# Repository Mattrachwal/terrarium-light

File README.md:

# Terrarium Light

techplants first electronic device

## Goal

A small low power terrarium light designed to sit on top of mini terrariums. 8x8x8 is probable max size of terrarium this would be usefull on.

## Parts List

ALED7709ATR

SPMWHD32AMH0XAR0PR

AL8860WT
https://www.diodes.com/assets/Datasheets/AL8860.pdf

CH340C

UMH3N
https://fscdn.rohm.com/en/products/databook/datasheet/discrete/transistor/digital/umh3ntn-e.pdf

TPS61169DCKR
https://www.ti.com/product/TPS61169

LDO voltage regulator

https://www.lcsc.com/datasheet/lcsc_datasheet_1811131510_MICRONE-Nanjing-Micro-One-Elec-ME6211C33M5G-N_C82942.pdf

This is the typical LDO used ona lot of dev boards
using the TO-263 for thermal reason, its overkill but i dont know how hot the whole board will be with the LEDS

HGSEMI LM1117S-3.3/TR
https://www.lcsc.com/datasheet/lcsc_datasheet_2209211201_HGSEMI-LM1117S-3-3-TR_C498315.pdf

NSR0240P2
https://www.onsemi.com/pdf/datasheet/nsr0240p2-d.pdf

BAS40

https://www.mouser.com/ProductDetail/Diotec-Semiconductor/SK16?qs=OlC7AqGiEDm3ojchOaQs2w%3D%3D

L coil thing
VLS6045EX-100M-H

USB C gotta pick party

https://www.lcsc.com/datasheet/lcsc_datasheet_2211161000_HCTL-HC-TYPE-C-16P-01A_C2894897.pdf

CAPACITORS

100nf = 0.1uF
https://www.digikey.com/en/products/detail/yageo/CC0805MRX7R9BB104/5884281?s=N4IgTCBcDaIMJwAwA5EFYCyAlAGgdiwE4AhYgRkQBYQBdAXyA
CC0805MRX7R9BB104
https://jlcpcb.com/partdetail/Yageo-CC0805MRX7R9BB104/C5182436

4.7uf
GRT21BR61H475ME13L

10uf
CC0805MKX5R5BB106
https://jlcpcb.com/partdetail/Yageo-CC0805MKX5R5BB106/C527238
https://www.digikey.com/en/products/detail/yageo/CC0805MKX5R5BB106/2833626?s=N4IgTCBcDaIMJwAwA5EFYCyBpAGmgSmgEJECMiAbCALoC%2BQA

22uF
https://jlcpcb.com/partdetail/Tdk-C2012X5R1C226MT000E/C329947
https://www.digikey.com/en/products/detail/tdk-corporation/C2012X5R1C226M125AC/2733082?s=N4IgTCBcDaIMJgAwEYwA0CsAlZCwDYBZAFUTIFEQBdAXyA

1uf
GCM219R71C105KA37D
https://www.digikey.com/en/products/detail/murata-electronics/GCM219R71C105KA37D/2592214?s=N4IgTCBcDaIOIGECyYCMBOASgdlQ1ADAKwDSAggMzYAiIAugL5A
https://jlcpcb.com/partdetail/2259442-GCM219R71C105KA37D/C2167390

RESISTOR
5.1k
RC0805FR-075K1L
https://jlcpcb.com/partdetail/Yageo-RC0805FR075K1L/C84375
RC0805FR-075K1L

2ohm
RC0805JR-072RL
https://jlcpcb.com/parts/componentSearch?searchTxt=RC0805JR-072RL
https://www.digikey.com/en/products/detail/yageo/RC0805JR-072RL/728267

ferriteBead

MI0805K400R-10

https://jlcpcb.com/partdetail/EspressifSystems-ESP32_S3_MINI_1N8/C2913206

dedcoupling/bipass capacitors. at least .1uF VCC PIN ON ALL VCC PINS

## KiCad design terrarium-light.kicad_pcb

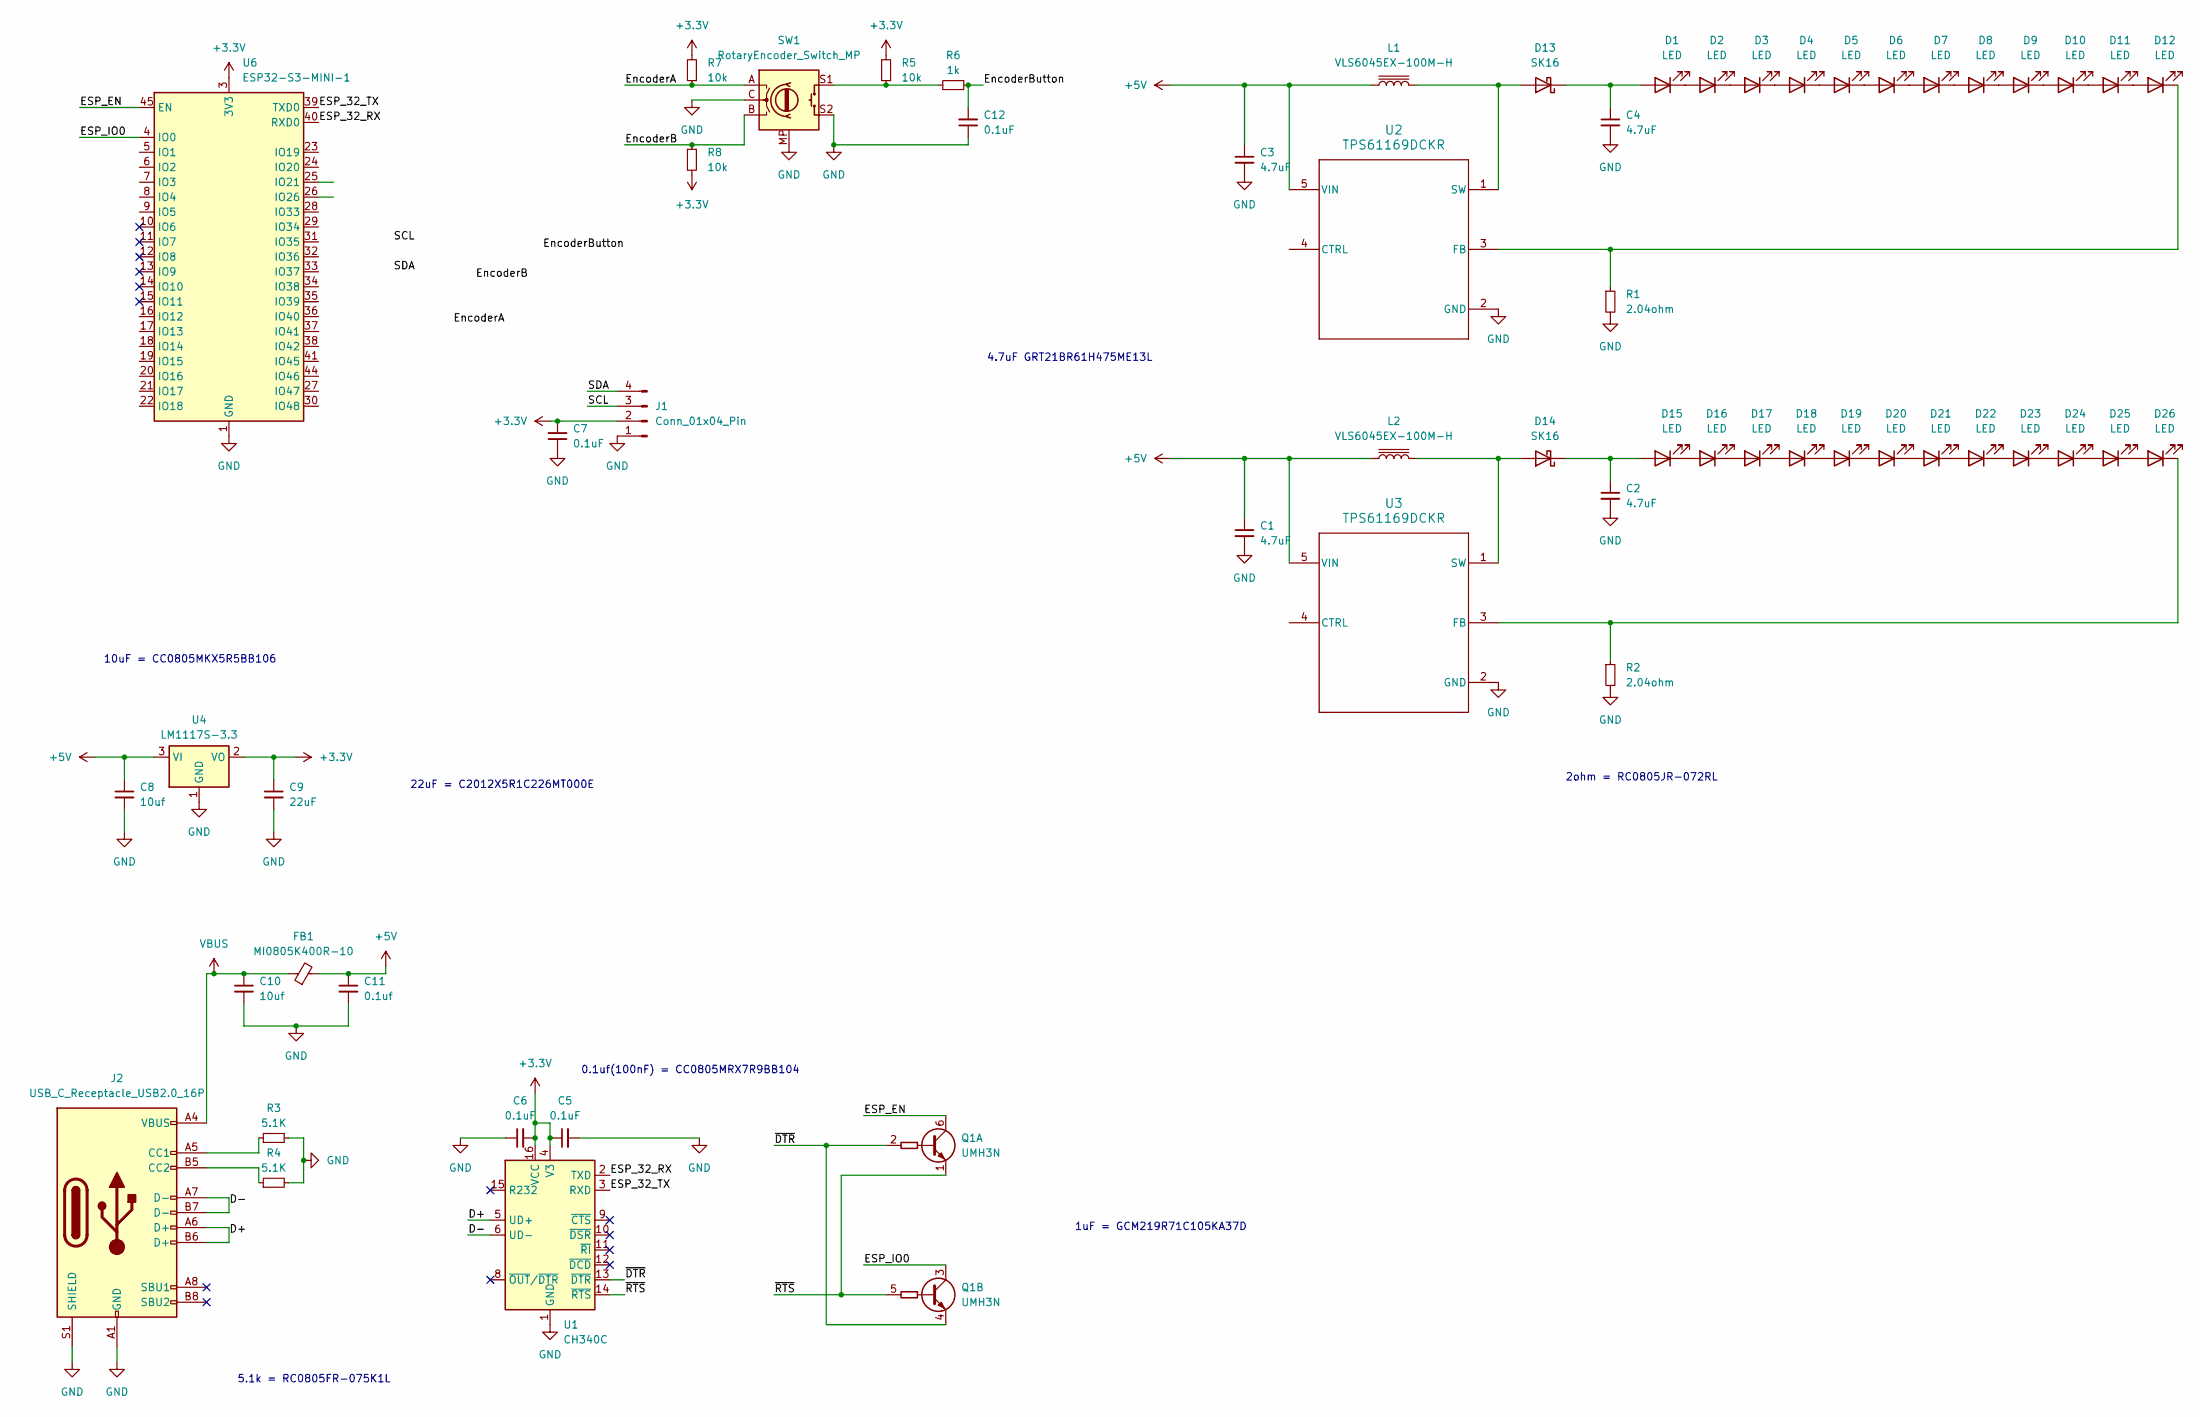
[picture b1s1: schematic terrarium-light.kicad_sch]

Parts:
C1, C2, C3, C4: 4.7uF; C_0805_2012Metric_Pad1.18x1.45mm_HandSolder
C5, C6, C7, C12: 0.1uF; C_0805_2012Metric_Pad1.18x1.45mm_HandSolder
C8, C10: 10uf; C_0805_2012Metric_Pad1.18x1.45mm_HandSolder
C9: 22uF; C_0805_2012Metric_Pad1.18x1.45mm_HandSolder
C11: 0.1uf; C_0805_2012Metric_Pad1.18x1.45mm_HandSolder
D1, D2, D3, D4, D5, D6, D7, D8, D9, D10, D11, D12, D15, D16, D17, D18, D19, D20, D21, D22, D23, D24, D25, D26: LED; LED_SPMWHD32AMH0XAR0PR
D13, D14: SK16; D_SMA_Handsoldering
FB1: MI0805K400R-10; R_0805_2012Metric_Pad1.20x1.40mm_HandSolder
J1: Conn_01x04_Pin; PinHeader_1x04_P2.54mm_Vertical
J2: USB_C_Receptacle_USB2.0_16P; USB_C_Receptacle_HCTL_HC-TYPE-C-16P-01A
L1, L2: VLS6045EX-100M-H; L_TDK_VLS6045EX_VLS6045AF
Q1: UMH3N; SOT-363_SC-70-6
R1, R2: 2.04ohm; R_0805_2012Metric_Pad1.20x1.40mm_HandSolder
R3, R4: 5.1K; R_0805_2012Metric_Pad1.20x1.40mm_HandSolder
R5, R7, R8: 10k; R_0805_2012Metric_Pad1.20x1.40mm_HandSolder
R6: 1k; R_0805_2012Metric_Pad1.20x1.40mm_HandSolder
SW1: RotaryEncoder_Switch_MP; RotaryEncoder_Alps_EC12E-Switch_Vertical_H20mm_CircularMoun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
U1: CH340C; SOIC-16_3.9x9.9mm_P1.27mm
U2, U3: TPS61169DCKR; SOT-353_SC-70-5_Handsoldering
U4: LM1117S-3.3; TO-263-3_TabPin2
U6: ESP32-S3-MINI-1; ESP32-S2-MINI-1

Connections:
+3.3V: C5.1, C6.2, C7.2, C9.1, J1.2, R5.2, R7.2, R8.2, U1.4 (V3), U1.16 (VCC), U4.2 (VO), U6.3 (3V3)
+5V: C1.1, C3.1, C8.1, C11.1, FB1.2, L1.1, L2.1, U2.5 (VIN), U3.5 (VIN), U4.3 (VI)
/D+: J2.A6 (D+), J2.B6 (D+), U1.5 (UD+)
/D-: J2.A7 (D-), J2.B7 (D-), U1.6 (UD-)
/ESP_32_RX: U1.2 (TXD), U6.40 (RXD0)
/ESP_32_TX: U1.3 (RXD), U6.39 (TXD0)
/ESP_EN: Q1.6 (C1), U6.45 (EN)
/ESP_IO0: Q1.3 (C2), U6.4 (IO0)
/EncoderA: R7.1, SW1.A
/EncoderB: R8.1, SW1.B
/EncoderButton: C12.2, R6.1
/SCL: J1.3
/SDA: J1.4
/~DTR: Q1.2 (B1), Q1.4 (E2), U1.13 (~DTR)
/~RTS: Q1.1 (E1), Q1.5 (B2), U1.14 (~RTS)
GND: C1.2, C2.2, C3.2, C4.2, C5.2, C6.1, C7.1, C8.2, C9.2, C10.2, C11.2, C12.1, J1.1, J2.A1 (GND), J2.A12 (GND), J2.B1 (GND), J2.B12 (GND), J2.S1 (SHIELD), R1.2, R2.2, R3.2, R4.2, SW1.C, SW1.MP, SW1.S2, U1.1 (GND), U2.2 (GND), U3.2 (GND), U4.1 (GND), U6.1 (GND), U6.2 (GND), U6.42 (GND), U6.43 (GND), U6.46 (GND), U6.47 (GND), U6.48 (GND), U6.49 (GND), U6.50 (GND), U6.51 (GND), U6.52 (GND), U6.53 (GND), U6.54 (GND), U6.55 (GND), U6.56 (GND), U6.57 (GND), U6.58 (GND), U6.59 (GND), U6.60 (GND), U6.61 (GND), U6.62 (GND), U6.63 (GND), U6.64 (GND), U6.65 (GND)
unnamed: C4.1, D1.2 (A), D13.1 (K)
unnamed: D1.1 (K), D2.2 (A)
unnamed: D2.1 (K), D3.2 (A)
unnamed: D3.1 (K), D4.2 (A)
unnamed: D4.1 (K), D5.2 (A)
unnamed: D5.1 (K), D6.2 (A)
unnamed: D6.1 (K), D7.2 (A)
unnamed: D7.1 (K), D8.2 (A)
unnamed: D8.1 (K), D9.2 (A)
unnamed: D9.1 (K), D10.2 (A)
unnamed: D10.1 (K), D11.2 (A)
unnamed: D11.1 (K), D12.2 (A)
unnamed: D12.1 (K), R1.1, U2.3 (FB)
unnamed: D13.2 (A), L1.2, U2.1 (SW)
unnamed: D14.2 (A), L2.2, U3.1 (SW)
unnamed: C2.1, D14.1 (K), D15.2 (A)
unnamed: D15.1 (K), D16.2 (A)
unnamed: D16.1 (K), D17.2 (A)
unnamed: D17.1 (K), D18.2 (A)
unnamed: D18.1 (K), D19.2 (A)
unnamed: D19.1 (K), D20.2 (A)
unnamed: D20.1 (K), D21.2 (A)
unnamed: D21.1 (K), D22.2 (A)
unnamed: D22.1 (K), D23.2 (A)
unnamed: D23.1 (K), D24.2 (A)
unnamed: D24.1 (K), D25.2 (A)
unnamed: D25.1 (K), D26.2 (A)
unnamed: D26.1 (K), R2.1, U3.3 (FB)
unnamed: J2.A5 (CC1), R3.1
unnamed: J2.B5 (CC2), R4.1
unnamed: R5.1, R6.2, SW1.S1
VBUS: C10.1, FB1.1, J2.A4 (VBUS), J2.A9 (VBUS), J2.B4 (VBUS), J2.B9 (VBUS)

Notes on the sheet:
4.7uF GRT21BR61H475ME13L
1uF = GCM219R71C105KA37D
22uF = C2012X5R1C226MT000E
2ohm = RC0805JR-072RL
10uF = CC0805MKX5R5BB106
5.1k = RC0805FR-075K1L
0.1uf(100nF) = CC0805MRX7R9BB104

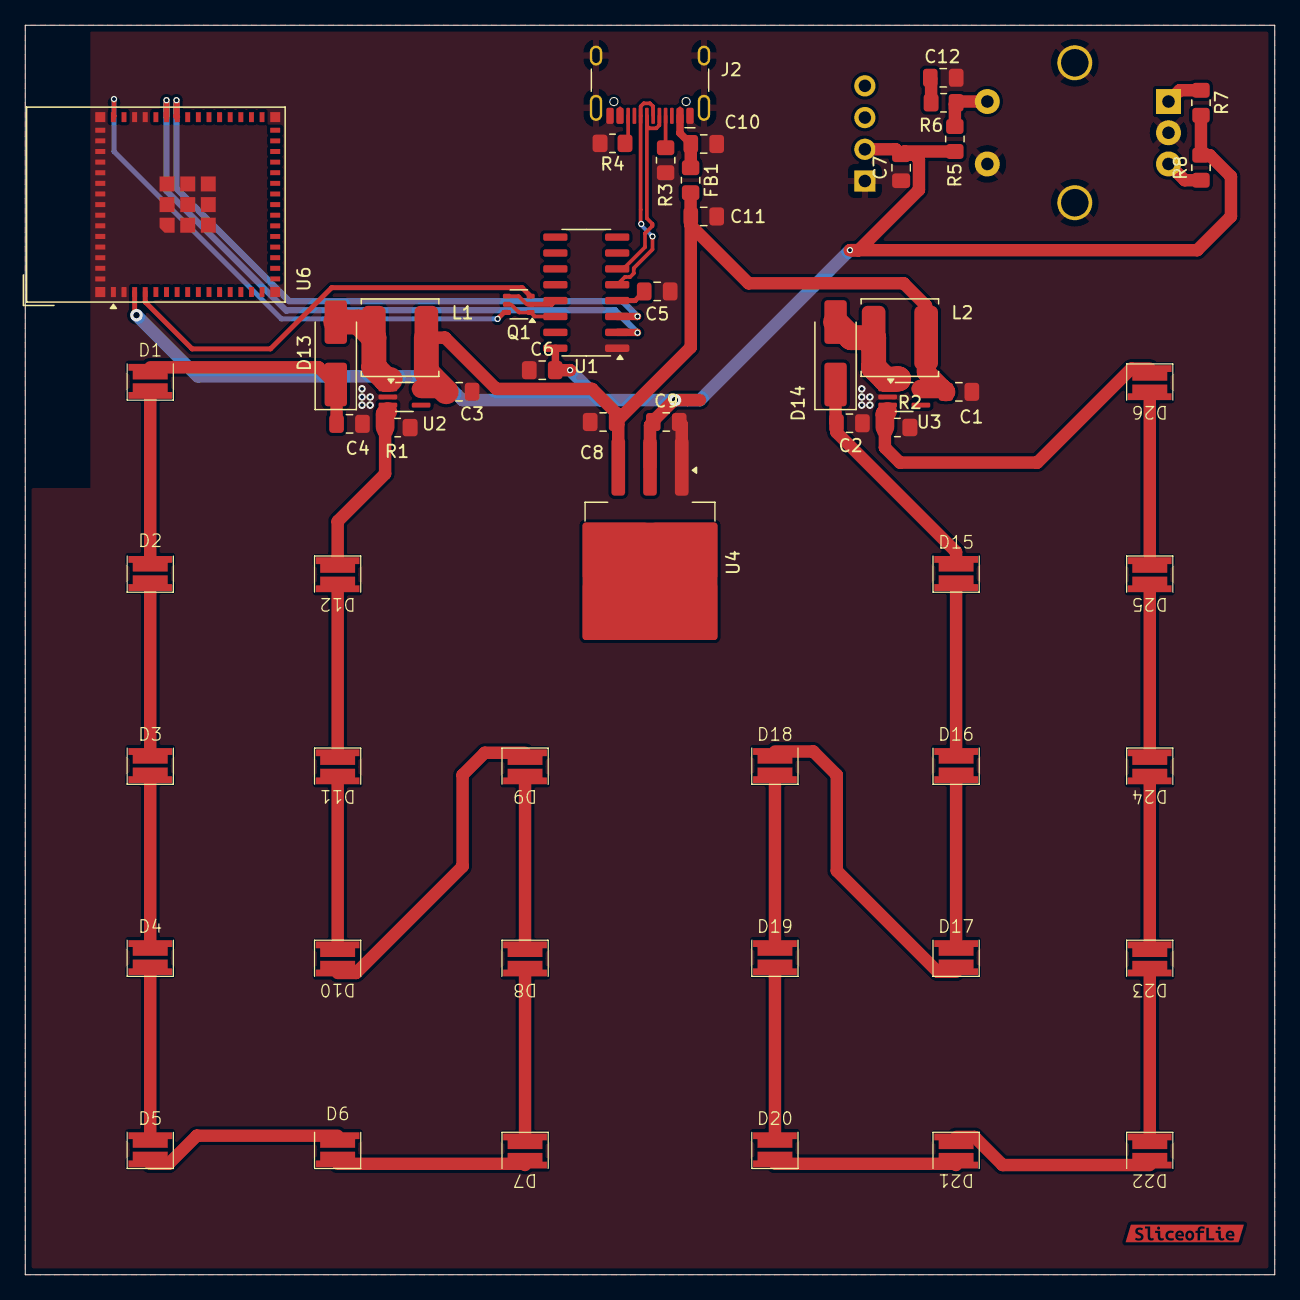
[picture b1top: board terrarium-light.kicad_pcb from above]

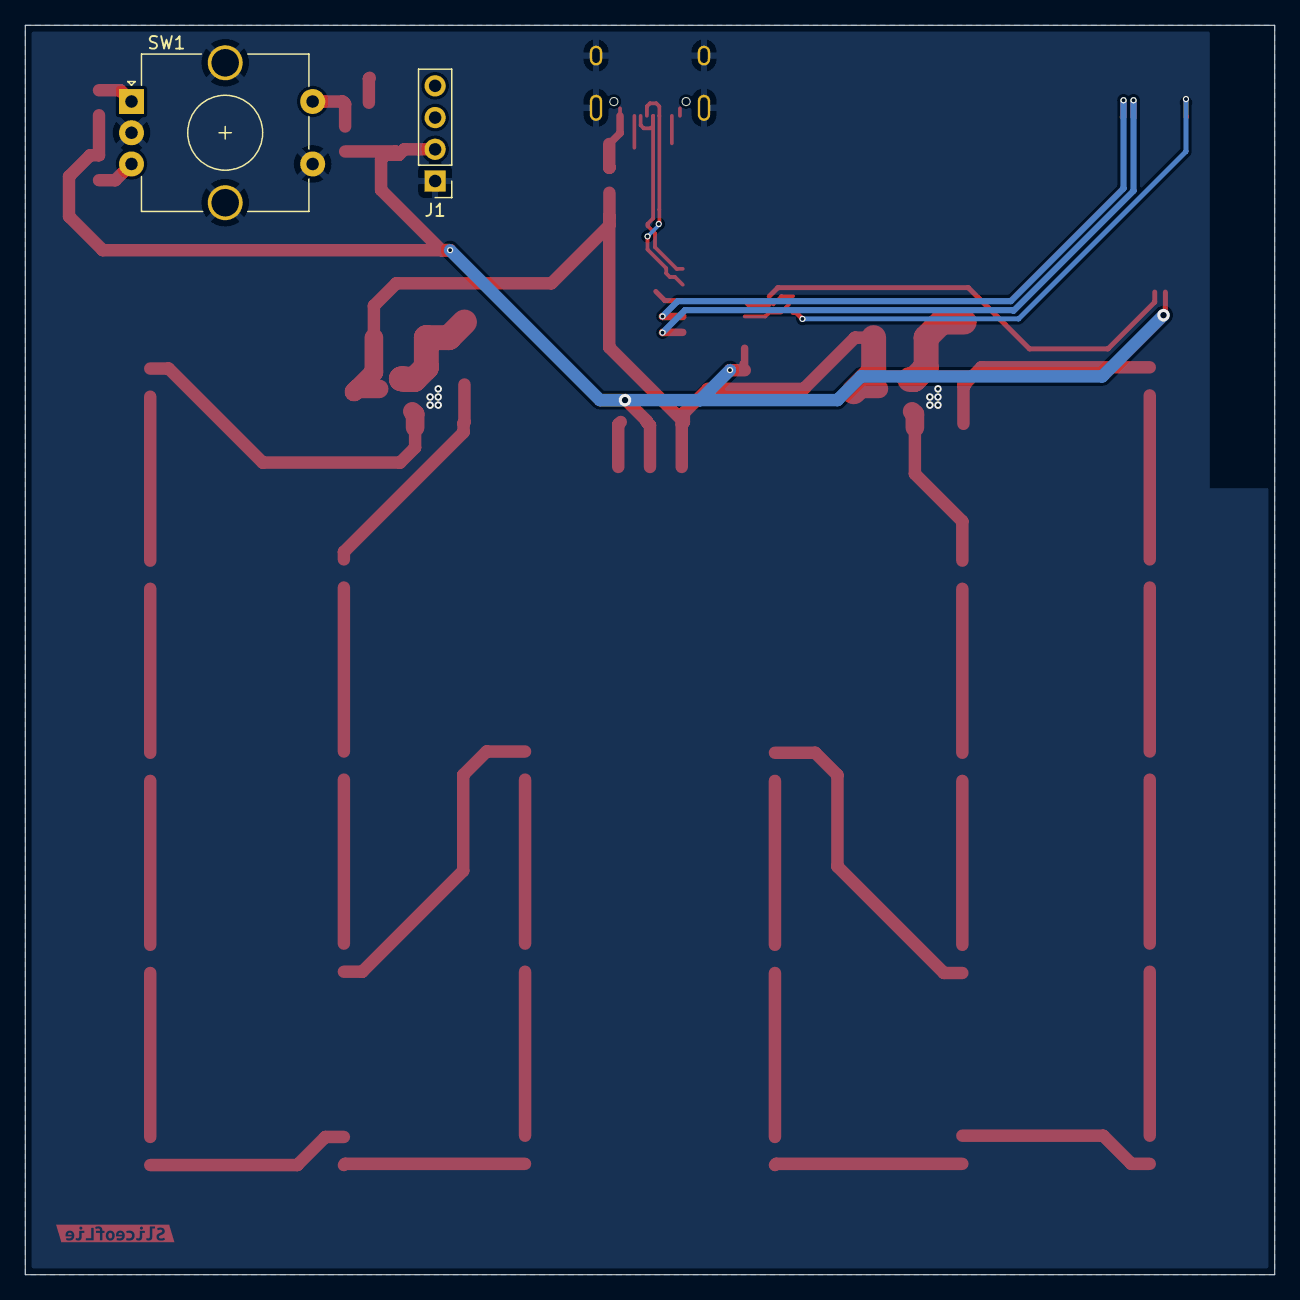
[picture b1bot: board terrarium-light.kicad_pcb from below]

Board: 2 copper layers, 100.0 x 100.0 mm, 59 parts (2 on the bottom side), 46 nets.

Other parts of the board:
kibuzzard-66CB9840: G***; kibuzzard-66CB9840

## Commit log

2024-03-10 new project init
2024-03-10 found a new part '
2024-03-10 moved some files
2024-03-13 CH340C seems good
2024-03-13 saved
2024-03-17 what
2024-03-17 notes
2024-03-17 ref image
2024-03-18 added footprint
2024-03-18 tried to add some stuff
2024-03-24 done
2024-03-24 updated the pad
2024-03-25 added parts
2024-03-27 found more parts and added them
2024-03-28 more stuff
2024-03-29 big redo
2024-03-31 better layout
2024-03-31 more layout
2024-04-01 re do
2024-04-11 LOTS OF MOVING
2024-05-06 big changes and lots of routing
2024-05-06 little more routing
2024-05-21 SO many changes
2024-06-08 big updates
2024-08-15 saving
2024-08-26 settings
2024-09-07 fixed
